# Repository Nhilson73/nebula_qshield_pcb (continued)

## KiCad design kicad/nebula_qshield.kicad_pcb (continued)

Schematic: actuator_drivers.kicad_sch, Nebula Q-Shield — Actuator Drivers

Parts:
C27: 100nF; C_0402_1005Metric
D10, D11, D14: SS34; D_SMA
D12, D13: 1N4148W; D_SOD-323
F2: 1A PTC; Fuse_0805_2012Metric; MPN MF-PSMF110X-2
F3: 0.5A PTC; Fuse_0805_2012Metric; MPN MF-PSMF050X-2
F4: 0.5A PTC; Fuse_0805_2012Metric
J17: Motor 12V; TerminalBlock_Phoenix_PT-1,5-2-5.0-H_1x02_P5.00mm_Horizontal; MPN 1757229
J18: CO2 Solenoid; TerminalBlock_Phoenix_PT-1,5-2-5.0-H_1x02_P5.00mm_Horizontal
J19: Chiller; TerminalBlock_Phoenix_PT-1,5-2-5.0-H_1x02_P5.00mm_Horizontal
J22: CO2 Valve; PhoenixContact_MC_1,5_2-G-3.81_1x02_P3.81mm_Horizontal; MPN 1757229
K1: HF46F-12-HS1; Relay_SPDT_Omron_G5V-1; MPN HF46F-12-HS1; Digi-Key_PN 255-5799-ND
K2: HF46F-12-HS1; Relay_SPDT_Omron_G5V-1
Q1: IRLZ44NPBF; TO-220-3_Vertical; MPN IRLZ44NPBF; Digi-Key_PN IRLZ44NPBF-ND
Q2, Q5: IRLZ44NPBF; TO-220-3_Vertical
Q3, Q4: 2N7002; SOT-23
R24, R25, R26, R27: 1k; R_0402_1005Metric
R28: 10k; R_0402_1005Metric
U16: PC817X2NIP; DIP-8_W7.62mm; MPN PC817X2NIP
U17: IR2104SPBF; SOIC-8_3.9x4.9mm_P1.27mm; MPN IR2104SPBF; Digi-Key_PN IR2104SPBF-ND
U18, U19: PC817X1NIP; DIP-4_W7.62mm
U20: MCP6002; SOIC-8_3.9x4.9mm_P1.27mm

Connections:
/5V_RAIL: U20.8 (V+); also elsewhere on the board
/12V_RAIL: D10.1 (K), D12.1 (K), D13.1 (K), D14.1 (K), K1.2, K2.2, Q1.2 (D), U17.1 (VCC), U17.3 (~SD); also elsewhere on the board
/Actuator Drivers/CHILLER_ISO: Q4.1 (G), U19.4
/Actuator Drivers/CHILLER_NO: F4.1, K2.10
/Actuator Drivers/CHILLER_OUT: F4.2, J19.1, K2.1
/Actuator Drivers/CO2_PWM_FILT: C27.1, R28.1, U20.5 (+)
/Actuator Drivers/CO2_PWM_OUT: Q5.1 (G), U20.6 (-), U20.7
/Actuator Drivers/CO2_SOL_ISO: Q3.1 (G), U18.4
/Actuator Drivers/CO2_SOL_NO: F3.1, K1.10
/Actuator Drivers/CO2_SOL_OUT: F3.2, J18.1, K1.1
/Actuator Drivers/CO2_VALVE: D14.2 (A), Q5.2 (D)
/Actuator Drivers/K1_COIL_N: D12.2 (A), K1.9, Q3.3 (D)
/Actuator Drivers/K2_COIL_N: D13.2 (A), K2.9, Q4.3 (D)
/Actuator Drivers/MOTOR_HO: Q1.1 (G), U17.7 (HO)
/Actuator Drivers/MOTOR_LO: Q2.1 (G), U17.5 (LO)
/Actuator Drivers/MOTOR_VB: F2.2, J17.1, U17.8 (VB)
/Actuator Drivers/MOTOR_VS: D10.2 (A), D11.1 (K), F2.1, Q1.3 (S), Q2.2 (D), U17.6 (VS)
/Actuator Drivers/PUMP_DIR_ISO: U16.4, U17.2 (IN)
/Actuator Drivers/U16_INA: R24.2, U16.1
/Actuator Drivers/U18_IN: R26.2, U18.1
/Actuator Drivers/U19_IN: R27.2, U19.1
/CHILLER_CTL: R27.1; also elsewhere on the board
/CO2_PWM: R28.2; also elsewhere on the board
/CO2_SOL_CTL: R26.1; also elsewhere on the board
/PUMP_DIR: R24.1; also elsewhere on the board
/PUMP_PWM: R25.1; also elsewhere on the board
GND: C27.2, D11.2 (A), J17.2, J18.2, J19.2, Q2.3 (S), Q3.2 (S), Q4.2 (S), Q5.3 (S), R25.2, U16.2, U16.3, U17.4 (COM), U18.2, U18.3, U19.2, U19.3, U20.3 (+), U20.4 (V-); also elsewhere on the board
unnamed: U20.1, U20.2 (-)

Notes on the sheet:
ACTUATOR DRIVERS — All opto-isolated from MCU Motor/recirculation: IR2104 + IRLZ44N (Insight+) Gas solenoid (CO2/H2): PC817 + 2N7002 + HF46F (Insight+) Chiller relay: PC817 + 2N7002 + HF46F (Insight+) CO2 PWM proportional valve: DNP all tiers (single gas via solenoid)
GAS SOLENOID RELAY (CO2/H2) — Insight+ MCU CO2_SOL_CTL → R26 → U18 → Q3 → Relay K1 → J18
CHILLER RELAY — Insight+ MCU CHILLER_CTL → R27 → U19 → Q4 → Relay K2 → J19
GAS PWM FLOW REGULATOR — DNP all tiers Single gas output uses solenoid K1/J18; U20/Q5/D14/R28/C27/J22 not populated
U20 unused sections

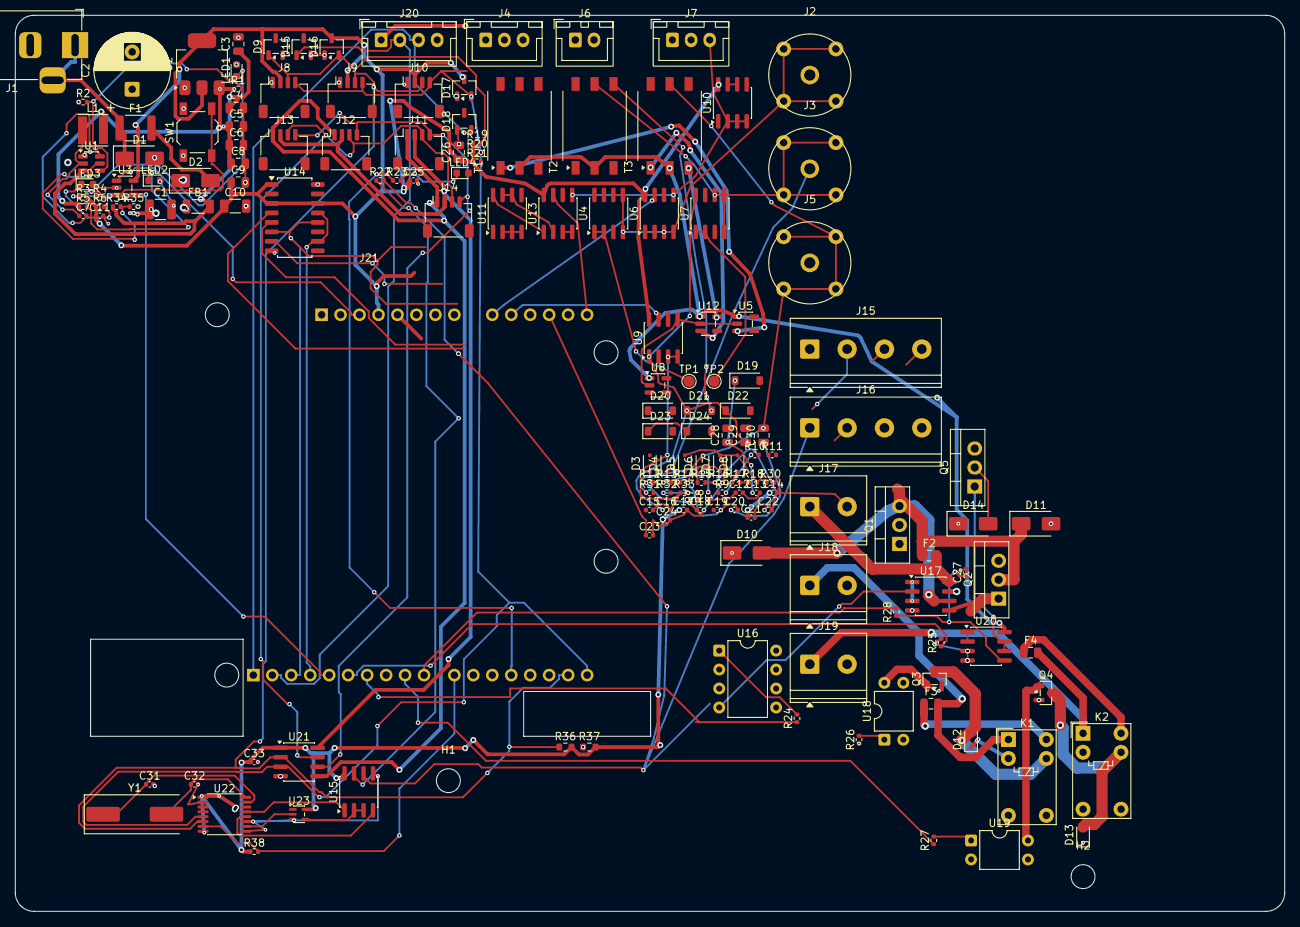
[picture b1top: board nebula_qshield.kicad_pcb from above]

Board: 4 copper layers, 170.0 x 120.0 mm, 164 parts (0 on the bottom side), 105 nets.

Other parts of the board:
D15: PESD3V3S2USF; SOT-23-3
D16, D17, D18: BAT54S; SOT-23-3
H1, H2: MountingHole_3.2mm_M3
J20: J20; JST_XH_B4B-XH-A_1x04_P2.50mm_Vertical
J21: Arduino UNO Q Shield; Arduino_UNO_Q_Shield
R36, R37: 4.7k; R_0603_1608Metric

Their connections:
/3V3_RAIL: D16.3, D17.3, J21.4, R36.2, R37.2; also elsewhere on the board
/5V_RAIL: D18.3, J20.1, J21.5; also elsewhere on the board
/12V_RAIL: J21.8; also elsewhere on the board
/CHILLER_CTL: J21.23; also elsewhere on the board
/CO2_ADC: J21.13; also elsewhere on the board
/CO2_PWM: J21.24; also elsewhere on the board
/CO2_SOL_CTL: J21.22; also elsewhere on the board
/DO_ADC: J21.14; also elsewhere on the board
/HMI & Connectors/HMI_RX: D18.2, J20.3, J21.15
/HMI & Connectors/HMI_TX: D15.1, J20.2, J21.16
/HUM_ADC: J21.12; also elsewhere on the board
/HX711_DOUT: J21.17; also elsewhere on the board
/HX711_SCK: J21.18; also elsewhere on the board
/I2C_SCL: D17.2, J21.32, R37.1; also elsewhere on the board
/I2C_SDA: D16.2, J21.31, R36.1; also elsewhere on the board
/LED_STATUS: J21.28; also elsewhere on the board
/MCU_NRST: J21.3; also elsewhere on the board
/MCU_WDI: J21.19; also elsewhere on the board
/ORP_ADC: J21.10; also elsewhere on the board
/PH_ADC: J21.9; also elsewhere on the board
/PUMP_DIR: J21.21; also elsewhere on the board
/PUMP_PWM: J21.20; also elsewhere on the board
/RS485_IRQ: J21.25; also elsewhere on the board
/TEMP_ADC: J21.11; also elsewhere on the board
GND: D15.2, D16.1, D17.1, D18.1, J20.4, J21.6, J21.7, J21.29; also elsewhere on the board

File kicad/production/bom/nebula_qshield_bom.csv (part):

Reference,Qty,Value,Description,Footprint,MPN,Digi-Key_PN,Unit_Price_100,Tier_Essential,Tier_Insight,Tier_Signature
,,,,,,,,,,
,,,— POWER MANAGEMENT (power_management.kicad_sch) —,,,,,,,
J1,1,PJ-002AH,"DC barrel jack, 2.1x5.5mm, 12V input",THT,PJ-002AH,CP-002AH-ND,$0.75,YES,YES,YES
D1,1,SMAJ15A,"TVS diode, bidirectional, 15V 400W",SMA,SMAJ15A,SMAJ15ALFCT-ND,$0.35,YES,YES,YES
F1,1,"1.1A PTC","PTC resettable fuse, 1.1A hold / 2.2A trip",1812,MF-MSMF110/24X-2,MF-MSMF110/24X-2CT-ND,$0.42,YES,YES,YES
D2,1,SS34,"Schottky diode, 40V 3A, reverse polarity",SMA,SS34,SS34-E3/57TCT-ND,$0.28,YES,YES,YES
C1,1,"100uF/25V","MLCC, input filter",1210,GRM32ER61E107ME20L,490-GRM32ER61E107ME20LCT-ND,$0.85,YES,YES,YES
C2,1,"470uF/25V","Electrolytic, bulk input",Radial_D10,UCD1E471MNL1GS,493-UCD1E471MNL1GSCT-ND,$0.45,YES,YES,YES
FB1,1,"600R@100MHz","Ferrite bead, 2A",1206,BLM31PG601SN1L,490-5222-1-ND,$0.12,YES,YES,YES
U1,1,TPS54302DDCR,"Buck converter, 4.5-28V in, 5V/3A out",SOT-23-6,TPS54302DDCR,296-50420-1-ND,$1.25,YES,YES,YES
L1,1,"4.7uH/4A","Power inductor, 4x4x2mm",4x4x2mm,744043004700,732-1260-1-ND,$0.48,YES,YES,YES
"C3,C4",2,"22uF/25V","MLCC, buck input X5R",0805,GRM21BR61E226ME44L,490-GRM21BR61E226ME44LCT-ND,$0.28,YES,YES,YES
"C5,C6",2,"47uF/10V","MLCC, buck output X5R",0805,GRM21BR61A476ME15L,490-GRM21BR61A476ME15LCT-ND,$0.35,YES,YES,YES
C7,1,"100nF","MLCC, bootstrap X7R 50V",0402,CL05B104KO5NNNC,1276-1001-1-ND,$0.01,YES,YES,YES
R1,1,"100k 1%","Feedback divider top (buck)",0402,CRCW0402100KFKED,541-100KLCT-ND,$0.02,YES,YES,YES
R2,1,"24.9k 1%","Feedback divider bottom (buck)",0402,CRCW040224K9FKED,541-24.9KLCT-ND,$0.02,YES,YES,YES
U2,1,AMS1117-3.3,"LDO regulator, 3.3V 800mA",SOT-223,AMS1117-3.3,AMS1117-3.3CT-ND,$0.32,YES,YES,YES
C8,1,"10uF/10V","MLCC, LDO input X5R",0805,GRM21BR61A106KE19L,490-GRM21BR61A106KE19LCT-ND,$0.08,YES,YES,YES
C9,1,"22uF/10V","MLCC, LDO output X5R",0805,GRM21BR61A226ME44L,490-GRM21BR61A226ME44LCT-ND,$0.12,YES,YES,YES
C10,1,"10uF/10V Tant","Tantalum, LDO stability",1206,T491A106M010AT,399-T491A106M010ATCT-ND,$0.18,YES,YES,YES
U3,1,TPS3823-33DBVR,"Voltage supervisor + watchdog, 3.3V threshold",SOT-23-5,TPS3823-33DBVR,296-34371-1-ND,$0.40,YES,YES,YES
SW1,1,RESET,"Manual reset button for TPS3823",SMD_TL3342,TL3342F160QG,EG2531CT-ND,$0.15,YES,YES,YES
R3,1,"10k","Pull-up for TPS3823 WDI",0402,CRCW040210K0JNED,541-10.0KJCT-ND,$0.01,YES,YES,YES
C11,1,"100nF","Decoupling for TPS3823 VDD",0402,CL05B104KO5NNNC,1276-1001-1-ND,$0.01,YES,YES,YES
LED1,1,Red,"LED indicator, 12V presence",0603,150060RS75000,732-150060RS75000CT-ND,$0.05,YES,YES,YES
LED2,1,Green,"LED indicator, 5V OK",0603,150060GS75000,732-150060GS75000CT-ND,$0.05,YES,YES,YES
LED3,1,Blue,"LED indicator, 3.3V OK",0603,150060BS75000,732-150060BS75000CT-ND,$0.08,YES,YES,YES
R4,1,"4.7k","LED current limit (12V, LED1)",0402,CRCW04024K70JNED,541-4.70KJCT-ND,$0.01,YES,YES,YES
R5,1,"330R","LED current limit (5V, LED2)",0402,CRCW0402330RJNED,541-330JCT-ND,$0.01,YES,YES,YES
R6,1,"100R","LED current limit (3.3V, LED3)",0402,CRCW0402100RJNED,541-100JCT-ND,$0.01,YES,YES,YES
,,,,,,,,,,
,,,— ANALOG ACQUISITION (analog_acquisition.kicad_sch) —,,,,,,,
J2,1,BNC,"BNC receptacle, panel mount, pH probe",THT,31-221-RFX,ARF1065-ND,$1.85,YES,YES,YES
J3,1,BNC,"BNC receptacle, panel mount, ORP probe",THT,31-221-RFX,ARF1065-ND,$1.85,YES,YES,YES
J4,1,"JST-XH 3P","JST-XH header, CO2 pressure sensor",THT,B3B-XH-A(LF)(SN),455-2248-ND,$0.15,DNP,YES,YES
J5,1,BNC,"BNC receptacle, panel mount, DO probe",THT,31-221-RFX,ARF1065-ND,$1.85,DNP,YES,YES
J6,1,"JST-XH 2P","JST-XH header, NTC temperature",THT,B2B-XH-A(LF)(SN),455-2247-ND,$0.12,YES,YES,YES
J7,1,"JST-XH 3P","JST-XH header, humidity sensor",THT,B3B-XH-A(LF)(SN),455-2248-ND,$0.15,DNP,DNP,YES
D3,1,PESD5V0S1BSF,"TVS ESD, 5V clamp, pH channel",SOD-323F,PESD5V0S1BSF,568-13204-1-ND,$0.15,YES,YES,YES
D4,1,PESD5V0S1BSF,"TVS ESD, 5V clamp, ORP channel",SOD-323F,PESD5V0S1BSF,568-13204-1-ND,$0.15,YES,YES,YES
D5,1,PESD5V0S1BSF,"TVS ESD, 5V clamp, CO2 channel",SOD-323F,PESD5V0S1BSF,568-13204-1-ND,$0.15,DNP,YES,YES
D6,1,PESD5V0S1BSF,"TVS ESD, 5V clamp, DO channel",SOD-323F,PESD5V0S1BSF,568-13204-1-ND,$0.15,DNP,YES,YES
D7,1,PESD3V3S1BSF,"TVS ESD, 3.3V clamp, temp channel",SOD-323F,PESD3V3S1BSF,568-13206-1-ND,$0.15,YES,YES,YES
D8,1,PESD5V0S1BSF,"TVS ESD, 5V clamp, humidity channel",SOD-323F,PESD5V0S1BSF,568-13204-1-ND,$0.15,DNP,DNP,YES
"R7,R9,R11,R13,R15,R17",6,"1k 1%","RC filter series resistors, analog channels",0402,CRCW04021K00FKED,541-1.00KLCT-ND,$0.02,YES*,YES,YES
"C12,C15,C18,C19,C22,C23",6,"100nF","RC filter caps, X7R 50V, analog channels",0402,CL05B104KO5NNNC,1276-1001-1-ND,$0.01,YES*,YES,YES
"R8,R10,R12,R14,R16,R18",6,"10M","Pull-down bias resistors, analog channels",0402,CRCW040210M0JNED,541-10.0MJCT-ND,$0.01,YES*,YES,YES
"U4,U7,U10,U11",4,MCP6002-I/SN,"Dual op-amp, rail-to-rail, 1MHz GBW (buffer per channel)",SOIC-8,MCP6002-I/SN,MCP6002-I/SN-ND,$0.52,YES*,YES,YES
C24,1,"100nF","Op-amp VDD decoupling, 3V3_RAIL",0402,CL05B104KO5NNNC,1276-1001-1-ND,$0.01,YES,YES,YES
"U5,U8,U12",3,SN6501DBVR,"Transformer driver, isolated power (pH/ORP/DO)",SOT-23-5,SN6501DBVR,296-SN6501DBVRCT-ND,$0.95,YES*,YES,YES
"U6,U9,U13",3,AMC1301DWVR,"Analog isolation amplifier, ±250mV input, 2.5kV (pH/ORP/DO)",SOIC-8,AMC1301DWVR,296-AMC1301DWVRCT-ND,$2.85,YES*,YES,YES
"T1,T2,T3",3,750315371,"Center-tapped transformer, SN6501-compatible",Transformer_SMD:Transformer_Wuerth_750315371,750315371,732-13596-1-ND,$1.50,YES*,YES,YES
"D19,D20,D21,D22,D23,D24",6,BAT54,"Schottky rectifier, isolated supply (2 per channel)",SOD-323,BAT54,1727-BAT54115CT-ND,$0.06,YES*,YES,YES
"C28,C29,C30",3,"10uF","Reservoir cap, isolated supply rail",0805,GRM21BR61C106KE15L,490-GRM21BR61C106KE15LCT-ND,$0.10,YES*,YES,YES
"C13,C14,C16,C17,C20,C21",6,"100nF","Isolation barrier decoupling (2 per channel)",0402,CL05B104KO5NNNC,1276-1001-1-ND,$0.01,YES*,YES,YES
"R30,R31",2,"511 0.1%","pH input divider ÷2 (post-buffer attenuator, matched pair)",0402,ERA-2AEB5110X,P511DBCT-ND,$0.08,YES*,YES,YES
R32,1,"4.02k 0.1%","ORP input divider top ÷5 (post-buffer attenuator)",0402,ERA-2AEB4021X,P4.02KDBCT-ND,$0.08,YES*,YES,YES
R33,1,"1.00k 0.1%","ORP input divider bottom ÷5 (post-buffer attenuator)",0402,ERA-2AEB1001X,P1.00KDBCT-ND,$0.08,YES*,YES,YES
"TP1,TP2",2,TestPoint,"Buffer-output test/calibration pad (pH/ORP full-scale probe)",TestPoint_Pad_D1.5mm,N/A,N/A,$0.00,YES*,YES,YES
,,,,,,,,,,
,,,— DIGITAL I2C (digital_i2c.kicad_sch) —,,,,,,,
"R19,R20",2,"4.7k 1%","I2C pull-up resistors to 3.3V",0402,CRCW04024K70FKED,541-4.70KLCT-ND,$0.02,YES,YES,YES
D9,1,PESD3V3S2USF,"TVS ESD, dual-line I2C bus, 0.5pF",SOT-23-3,PESD3V3S2USF,568-13207-1-ND,$0.22,YES,YES,YES
"J8,J9,J10,J11,J12,J13,J14",7,"Qwiic 4P","JST-SH Qwiic header (I2C)",SMD,SM04B-SRSS-TB(LF)(SN),455-1804-1-ND,$0.32,YES*,YES*,YES
U14,1,HX711,"24-bit ADC, load cell, 80 SPS, gain 128",SOP-16,HX711,-(LCSC:C124335),$0.65,YES,YES,YES
J15,1,"Terminal 4P","Terminal block, load cell E+/E-/S+/S-",THT,1757242,277-1274-ND,$0.85,YES,YES,YES
R21,1,"10k","Pull-up on HX711 DOUT",0402,CRCW040210K0JNED,541-10.0KJCT-ND,$0.01,YES,YES,YES
C25,1,"100nF","HX711 decoupling, VDD",0402,CL05B104KO5NNNC,1276-1001-1-ND,$0.01,YES,YES,YES
C26,1,"10uF","HX711 decoupling, VSUP",0805,GRM21BR61A106KE19L,490-GRM21BR61A106KE19LCT-ND,$0.08,YES,YES,YES
U15,1,MAX3485CSA+,"RS485 transceiver, half-duplex, 3.3V (Hamilton)",SOIC-8,MAX3485CSA+,MAX3485CSA+-ND,$1.95,DNP,DNP,YES
J16,1,"Terminal 4P","Terminal block, RS485 (Hamilton)",THT,1757242,277-1274-ND,$0.85,DNP,DNP,YES
R22,1,"120R","RS485 termination resistor (DNP by default)",0402,-,-,$0.01,DNP,DNP,DNP
U22,1,SC16IS740,"I2C-to-UART bridge for Modbus RTU, 64-byte FIFO",TSSOP-16,SC16IS740IPW/Q900,568-13068-1-ND,$2.05,DNP,DNP,YES
U23,1,SN74LVC1G04,"Single inverter, RS485 direction control polarity",SOT-353,SN74LVC1G04DCKR,296-11602-1-ND,$0.09,DNP,DNP,YES
Y1,1,"1.8432MHz","Crystal for SC16IS740 UART clock, 18pF",HC49-SD,ABLS-1.8432MHZ-B4-T,535-9930-1-ND,$0.42,DNP,DNP,YES
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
